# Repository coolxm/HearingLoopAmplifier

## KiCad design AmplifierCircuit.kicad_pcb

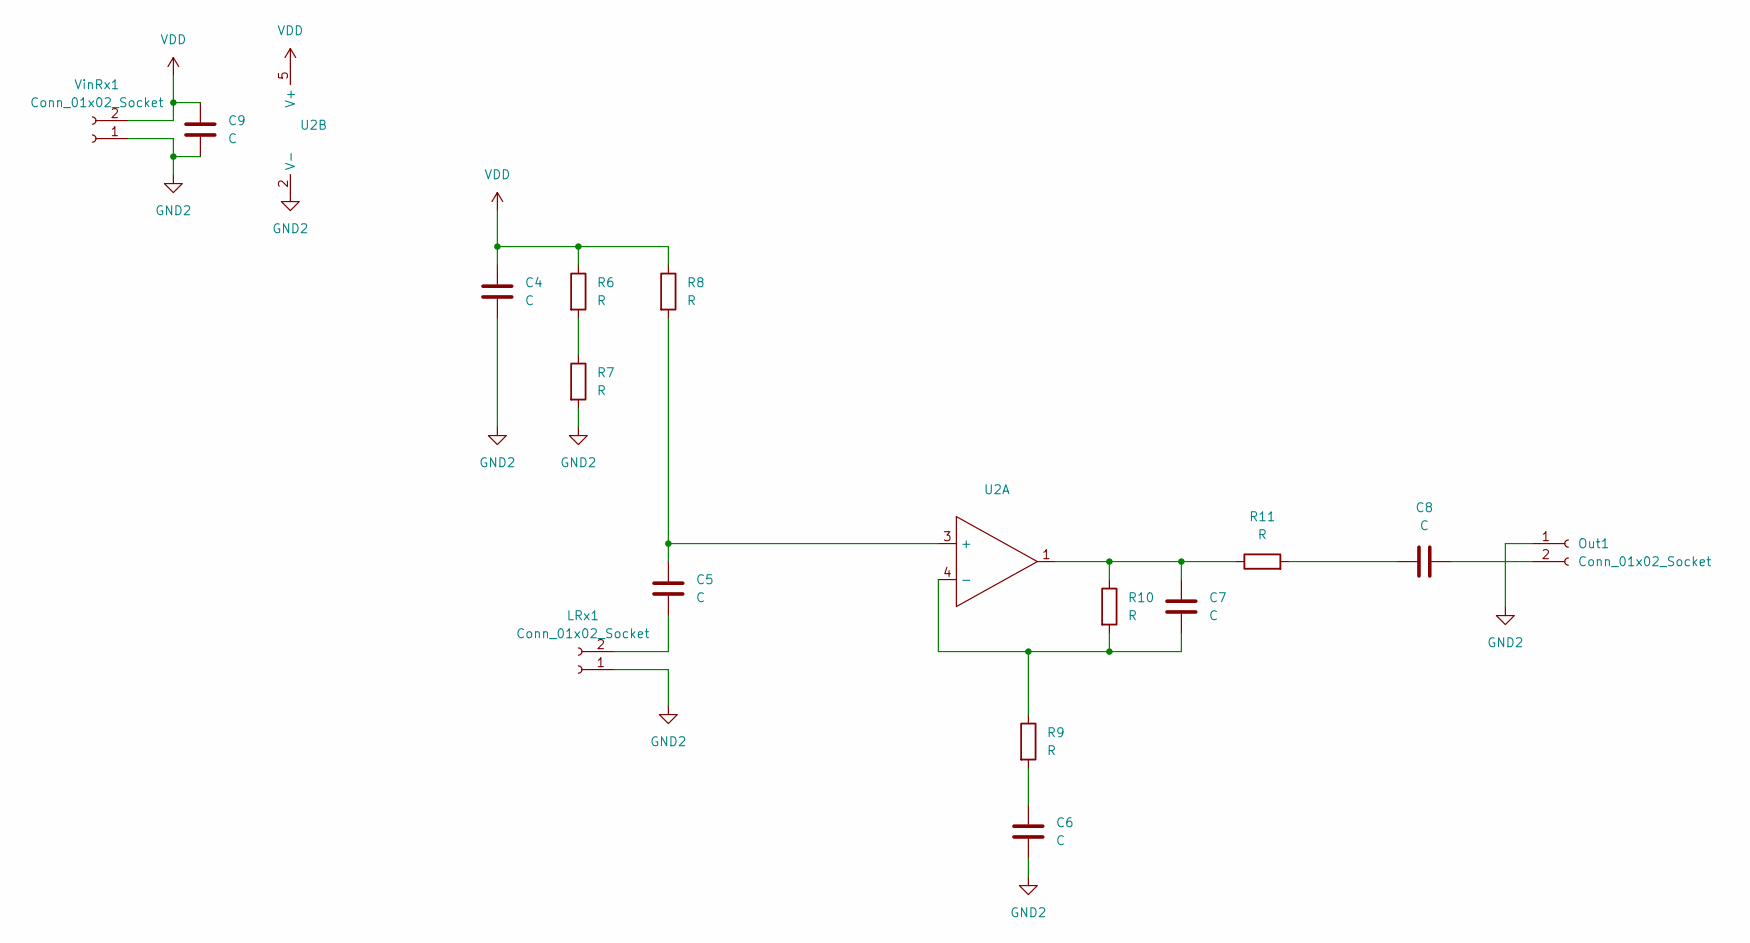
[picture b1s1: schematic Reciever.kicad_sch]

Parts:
C4, C5, C6, C7, C8, C9: C; C_Radial_D8.0mm_H11.5mm_P3.50mm
LRx1: Conn_01x02_Socket; PinSocket_1x02_P2.54mm_Vertical
Out1: Conn_01x02_Socket; PinSocket_1x02_P2.54mm_Vertical
R6, R7, R8, R9, R10, R11: R; R_Axial_DIN0309_L9.0mm_D3.2mm_P12.70mm_Horizontal
U2: SOT-23-5_HandSoldering
VinRx1: Conn_01x02_Socket; PinSocket_1x02_P2.54mm_Vertical

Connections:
GND2: C4.2, C6.2, C9.2, LRx1.1, Out1.1, R7.2, U2.2 (V-), VinRx1.1
unnamed: C6.1, R9.2
unnamed: C7.1, R10.1, R11.1, U2.1
unnamed: C8.1, R11.2
unnamed: C5.2, LRx1.2
unnamed: C8.2, Out1.2
unnamed: R6.2, R7.1
unnamed: C5.1, R8.2, U2.3 (+)
unnamed: C7.2, R9.1, R10.2, U2.4 (-)
VDD: C4.1, C9.1, R6.1, R8.1, U2.5 (V+), VinRx1.2

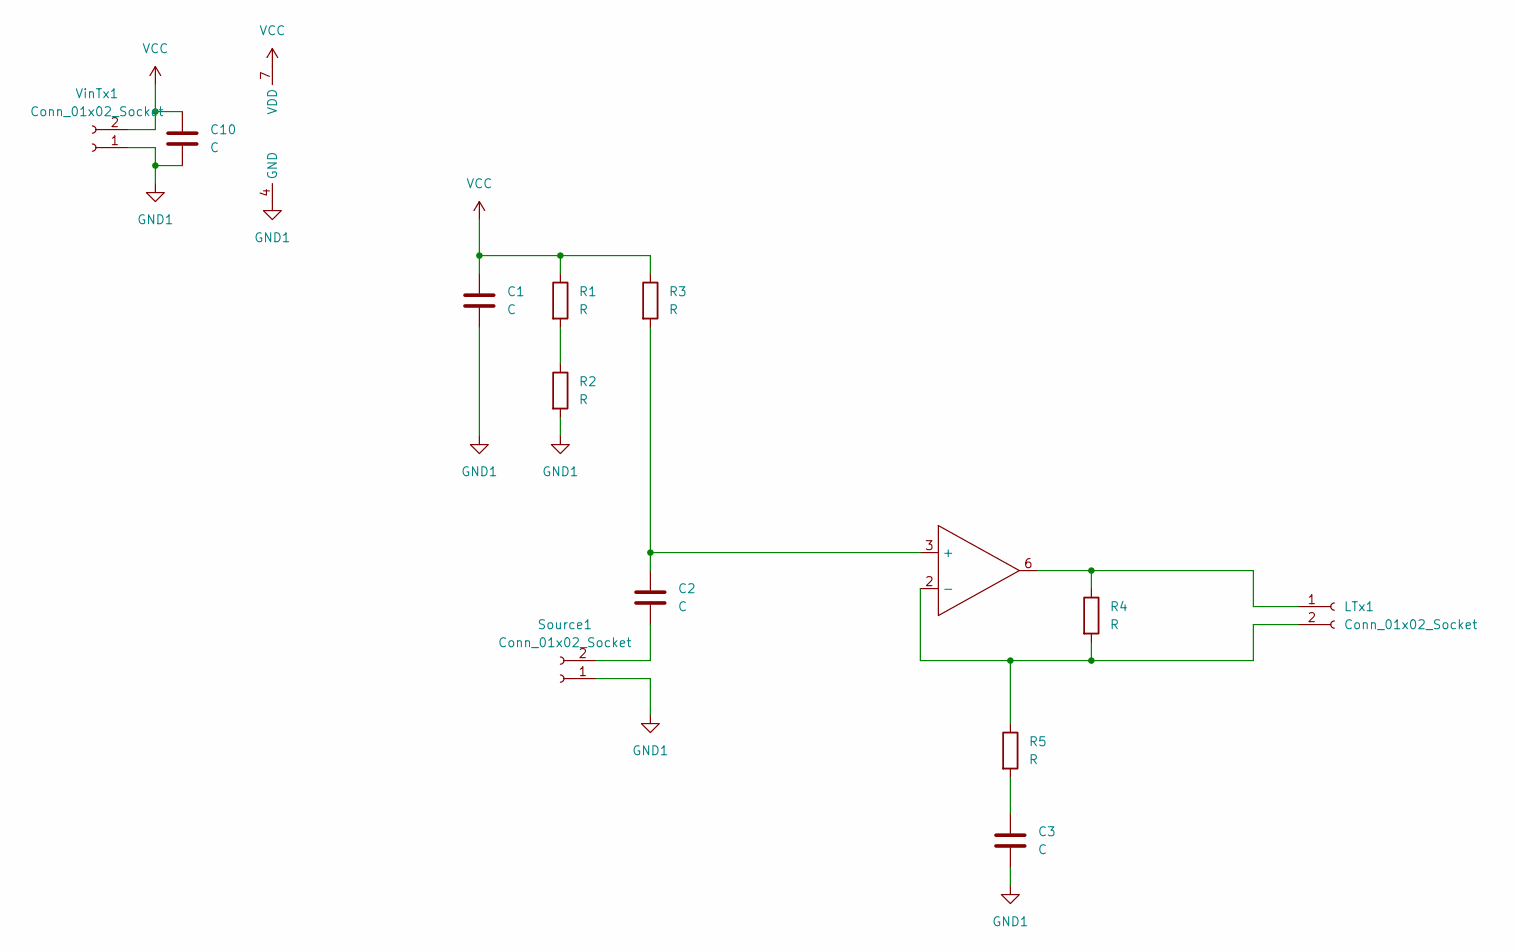
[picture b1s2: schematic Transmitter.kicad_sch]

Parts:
C1, C2, C3, C10: C; C_Radial_D8.0mm_H11.5mm_P3.50mm
LTx1: Conn_01x02_Socket; PinHeader_1x02_P2.54mm_Vertical
R1, R2, R3, R4, R5: R; R_Axial_DIN0309_L9.0mm_D3.2mm_P12.70mm_Horizontal
Source1: Conn_01x02_Socket; PinHeader_1x02_P2.54mm_Vertical
U1: SOIC-8_5.3x5.3mm_P1.27mm
VinTx1: Conn_01x02_Socket; PinSocket_1x02_P2.54mm_Vertical

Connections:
GND1: C1.2, C3.2, C10.2, R2.2, Source1.1, U1.4 (GND), VinTx1.1
unnamed: C3.1, R5.2
unnamed: LTx1.1, R4.1, U1.6
unnamed: LTx1.2, R4.2, R5.1, U1.2 (-)
unnamed: R1.2, R2.1
unnamed: C2.2, Source1.2
unnamed: C2.1, R3.2, U1.3 (+)
VCC: C1.1, C10.1, R1.1, R3.1, U1.7 (VDD), VinTx1.2

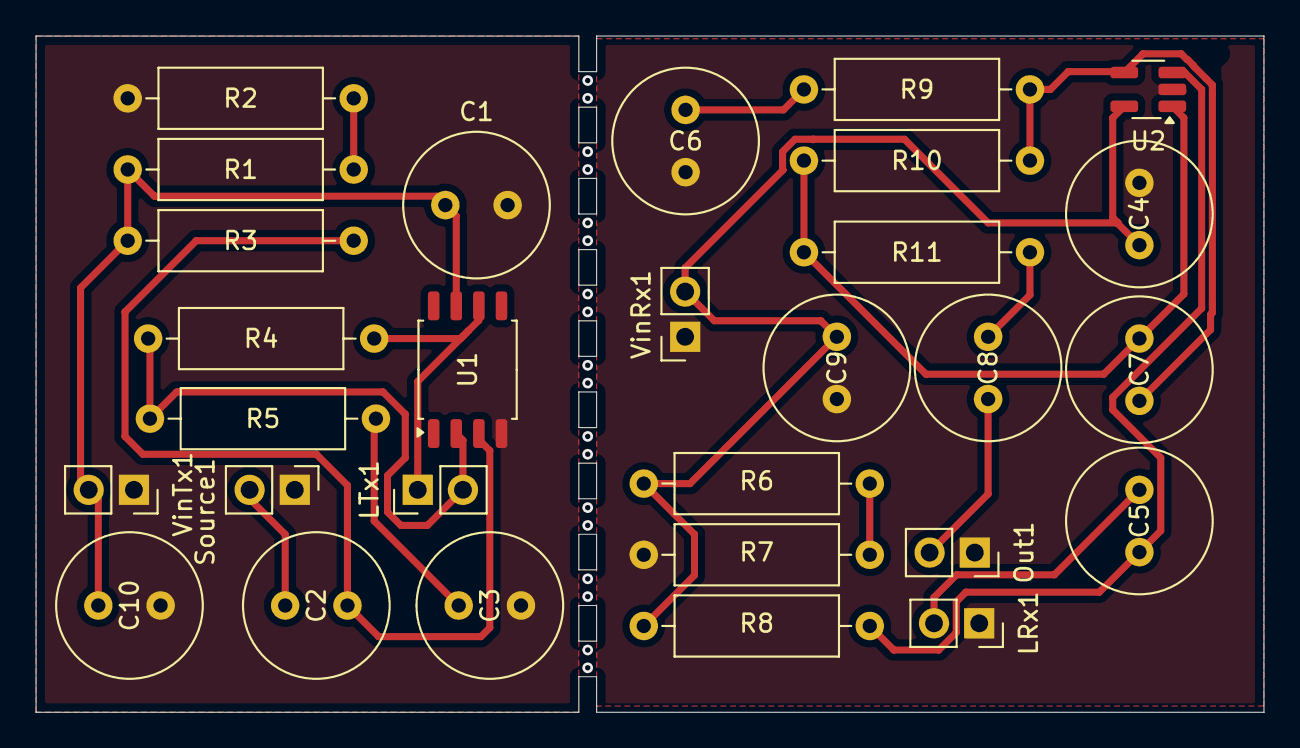
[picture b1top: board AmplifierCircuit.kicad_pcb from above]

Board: 2 copper layers, 69.0 x 38.0 mm, 29 parts (0 on the bottom side), 18 nets.

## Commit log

2025-04-02 Init Commit
2025-04-02 add gitignore
2025-04-02 Added PCB v1
2025-04-03 Updated the footprints for SMD
